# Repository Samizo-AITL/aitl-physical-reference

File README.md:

# 🧩 aitl-physical-reference

This repository provides a **minimal physical reference PCB**  
that anchors abstract control and logic concepts into **real voltage, current, and copper**.

It is intentionally **small, generic, and architecture-agnostic**,  
focusing on **observability, physical constraints, and manufacturability** rather than functionality.

---

## 🔗 Links

| Language | GitHub Pages 🌐 | GitHub 💻 |
|----------|----------------|-----------|
| 🇺🇸 English |  |  |

---

## 🎯 Purpose

The purpose of this board is **not control**, but **grounding**.

- 🔌 Fix abstract logic into **measurable V–I behavior**
- 👁 Provide a **visible and probe-able physical endpoint**
- 🧱 Act as a **lowest-level physical reference**, reusable across systems

This board can be *used by* higher-level architectures  
(control logic, supervisory layers, AI reasoning),  
but it **does not depend on them**.

---

## 🧩 What This Is

This repository contains a **reference PCB**, not a product.

The board includes only elements required to expose  
the relationship between logic and physics:

- 💡 **LED** — observable output state  
- 🧮 **Resistor** — physical constraint (current limitation)  
- 🔘 **Switch** — discrete physical event input  
- 📍 **Test Point** — voltage / current measurement access  
- 📐 **Board outline (Edge.Cuts)** — explicit physical boundary  

Nothing more.

---

## 🖼 Figure Index (Canonical)

All schematics, PCB layouts, and 3D views used in this project are
**normatively indexed and embedded** on the following page:

👉 **Image Index (v0–v3)**  
[https://samizo-aitl.github.io/aitl-physical-reference/docs/img/](https://samizo-aitl.github.io/aitl-physical-reference/docs/img/)

> v3 figures are provided for *derived control reference boards*
> and do not modify the normative v0–v2 physical reference.

---

## 🖼 Physical Reference Overview

### 1️⃣ Schematic (Logical → Physical Mapping)

This schematic defines the **normative logical–physical boundary**:  
a logic-driven output constrained by real voltage and current,  
with explicit measurement access points.

---

### 2️⃣ PCB Layout (Physical Constraints)

The PCB layout exposes the **fixed physical constraints**:

- 🟠 Copper routing and current paths  
- 📦 Component placement tied to observability  
- ⛓ Explicit board boundary (Edge.Cuts)  

This layout is the **authoritative physical truth** for v1.

---

### 3️⃣ 3D View (Embodied Reality)

The 3D view represents the **embodied boundary** between logic and physics:  
real height, real clearances, and real probe access —  
nothing abstracted, nothing implied.

---

## 🚫 What This Is NOT

- ❌ Not a full controller  
- ❌ Not MCU-centric  
- ❌ Not performance-optimized  
- ❌ Not tied to any single architecture or framework  
- ❌ Not a demo board for features  

This repository intentionally avoids *solutions* and focuses on *reference*.

---

## 🧠 Architecture Mapping (Conceptual → Physical)

| Conceptual Role | Physical Element |
|-----------------|------------------|
| Output state    | 💡 LED           |
| Constraint      | 🧮 Resistor      |
| Event input     | 🔘 Switch        |
| Observation     | 📍 Test point    |
| Boundary        | 📐 PCB outline   |

This mapping is the **core value** of the project.

---

## 🗂 Repository Structure

```
aitl-physical-reference/
├─ hardware/
│ └─ kicad/ # KiCad project (schematic / PCB)
├─ bom/
│ └─ bom.csv # Component list (non-CAD)
├─ docs/
│ ├─ Assembly.md # Assembly instructions
│ ├─ TestProcedure.md # Measurement & verification
│ └─ DesignIntent.md # Physical design intent
└─ README.md
```

---

## 📂 Key Artifacts (Reference Entry Points)

### 📄 Documentation
- **Design Intent**  
  [GitHub Page](https://samizo-aitl.github.io/aitl-physical-reference/docs/DesignIntent.html)  
  [Repository](https://github.com/Samizo-AITL/aitl-physical-reference/tree/main/docs/DesignIntent.md)

- **Assembly Instructions**  
  [GitHub Page](https://samizo-aitl.github.io/aitl-physical-reference/docs/Assembly.html)  
  [Repository](https://github.com/Samizo-AITL/aitl-physical-reference/tree/main/docs/Assembly.md)

- **Test & Measurement Procedure**  
  [GitHub Page](https://samizo-aitl.github.io/aitl-physical-reference/docs/TestProcedure.html)  
  [Repository](https://github.com/Samizo-AITL/aitl-physical-reference/tree/main/docs/TestProcedure.md)

### 🧾 Bill of Materials
- **BOM (CSV)**  
  [GitHub Page](https://samizo-aitl.github.io/aitl-physical-reference/bom/bom.csv)  
  [Repository](https://github.com/Samizo-AITL/aitl-physical-reference/blob/main/bom/bom.csv)

### 🧩 Hardware Source (Physical Truth)
- **KiCad Project (Schematic / PCB)**  
  [Repository](https://github.com/Samizo-AITL/aitl-physical-reference/tree/main/hardware/kicad)

---

## 🔧 Build & Assembly Flow

To physically build and use this reference board:

1. 📄 Review **`bom/bom.csv`** and prepare components  
2. 🏭 Manufacture PCB using KiCad data in `hardware/kicad/`  
3. 🛠 Assemble components following **`docs/Assembly.md`**  
4. ⚡ Apply +5V power and observe LED behavior  
5. 📊 Verify voltage/current using **`docs/TestProcedure.md`**

This flow is intentionally simple and repeatable.

---

## 📏 Verification & Measurement

This board is designed to be **measured**, not just powered.

Typical checks:

- 💡 LED ON/OFF state  
- 📍 Forward voltage at test point  
- 🧮 Current limited by resistor  
- 📐 Boundary defined by board outline  

These checks validate the **logic → physics transition**.

---

## 🧰 Toolchain

- 🧩 **CAD**: KiCad  
- 🎨 **Design style**: Minimal, readable, single-layer preferred  
- 📤 **Outputs**: Standard manufacturable Gerber data  

The design favors **clarity over density**.

---

## 🌍 Usage Context

This physical reference can be used in:

- 🎛 Control systems  
- 🧠 Supervisory logic  
- 🎓 Educational hardware  
- 🔁 Logic-to-physical architecture studies  
- 🤖 AITL-based discussions and validation  

It acts as a **ground truth layer**, not a controller.

---

## 📌 Status

- **v0** — Minimal physical reference  
  - 💡 LED  
  - 🧮 Resistor  
  - 🔘 Switch  
  - 📍 Test point  

Future revisions may extend observability,  
but will preserve minimalism.

---

## 🟦 v1 Definition — Physical ↔ Logical Boundary Reference

**v1** extends *aitl-physical-reference* from a passive grounding board  
into a **clearly defined physical–logical boundary reference**.

This version does **not** aim to control, compute, or decide.  
It exists solely to **define where logic ends and physics begins**.

---

### 🎯 Purpose of v1

- 🔗 Define a **clear GPIO ↔ physical boundary**
- 📏 Fix **measurable voltage–current expectations** at that boundary
- 🧭 Provide a **stable reference point** for higher layers (FSM / PID / AI)

v1 answers one question only:

> *“When logic toggles a pin, what does that mean in copper, voltage, and current?”*

---

### 🔌 v1 Scope (Strict)

v1 **adds a boundary**, not intelligence.

**Included**
- 📍 Explicit **logic-level input/output pins**
- 💡 Physical load (LED + R) driven *through* that boundary
- 📊 Documented **expected V–I ranges per node**
- 🧪 Test points tied to logical meaning

**Explicitly excluded**
- ❌ No firmware logic
- ❌ No control algorithm
- ❌ No timing guarantees
- ❌ No optimization

---

### 📐 Boundary Concept

| Layer | Responsibility |
|------|----------------|
| Logical / MCU | State decision, timing, abstraction |
| **v1 Boundary** | **Voltage level, current flow, observability** |
| Physical | Light emission, heat, copper limits |

v1 is the **line**, not the controller.

---

### 📊 Reference Measurement Table (Normative)

| Node | Condition | Expected Voltage | Expected Current | Meaning |
|-----|----------|-----------------|-----------------|--------|
| LOGIC_OUT | High | 3.3–5.0 V | < 1 mA | Logic asserts state |
| LED_NODE | ON | 1.8–2.2 V | 5–10 mA | Physical output active |
| VCC | Nominal | 5.0 V ±5% | — | Power reference |

This table is **normative** in v1.

---

### 🧠 Architectural Role

v1 serves as:

- 🔹 **FSM** — physical state confirmation point  
- 🔹 **PID** — actuator-side reality reference  
- 🔹 **LLM / AI** — grounding layer to prevent abstraction drift  

Higher layers may change.  
**v1 must not.**

---

### 🔒 Stability Rule

Once released:

> **v1 electrical meaning SHALL NOT change.**

Any extension must:
- become **v1.x** (documentation / measurement only), or
- move to **v2** (control-capable reference)

---

### 🏷 Versioning Summary

- 🟢 **v0** — Passive physical reference (LED / R / SW / TP)
- 🔵 **v1** — Logical–physical boundary reference
- 🟣 **v2** — Control-capable execution reference (FSM / PID)

---

## 🔖 GPIO Naming Rule (v1)

GPIO names in **v1** are **semantic and directional**.  
They describe **what crosses the boundary**, not how it is implemented.

### 📛 Naming Format

```
<ROLE>_<DIRECTION>
```

- **ROLE**: logical meaning at the boundary  
- **DIRECTION**: signal direction *from logic perspective*

### 📌 Standard Roles

| Name | Meaning |
|-----|--------|
| `LOGIC_OUT` | Logic asserts a physical state |
| `LOGIC_IN` | Logic observes a physical condition |
| `PWR_IN` | External power reference |
| `GND` | Electrical ground |

### 🔄 Direction Definition

- `_OUT` : logic → physical  
- `_IN`  : physical → logic  

> Example: `LOGIC_OUT` means  
> “Logic drives voltage/current into the physical layer.”

### 🚫 Prohibited in v1

- ❌ MCU-specific names (`PA0`, `GPIO23`)
- ❌ Functional assumptions (`LED_CTRL`, `PWM_OUT`)
- ❌ Timing semantics (`CLK`, `SYNC`)

v1 names must remain **architecture-agnostic and timeless**.

---

## 🟣 v2 Definition — Executable Physical Loop Reference

**v2** realizes the v1 physical–logical boundary  
as a **manufacturable, observable, and DRC-clean physical loop**.

While v1 defines *what the boundary means*,  
v2 defines *how that meaning exists in copper*.

---

### 🎯 Purpose of v2

- 🧱 Fix the **entire V–I loop** as a physical fact
- 👁 Preserve **observability at every critical node**
- 🏭 Ensure **manufacturability (DRC clean, Edge.Cuts defined)**
- 🚫 Still **no control logic, no firmware, no optimization**

v2 answers one question only:

> *“If we freeze the physical loop itself, what remains controllable?”*

---

### 🔌 v2 Scope (Strict)

**Included**
- 📐 Explicit **board outline (Edge.Cuts)**
- 🔁 Single, closed **physical current loop**
- 📍 Test points that do **not disturb** the loop
- 🧮 Current-limiting elements as physical constraints

**Explicitly excluded**
- ❌ No MCU
- ❌ No GPIO semantics
- ❌ No feedback or timing logic
- ❌ No intelligence

---

### 🧠 Architectural Role of v2

| Layer | Role |
|------|------|
| v1 | Normative boundary definition |
| **v2** | **Executable physical ground truth** |
| v3+ | Control, supervision, adaptation |

v2 is the **last layer before control begins**.

---

### 🔒 Stability Rule (v2)

Once released:

> **The physical loop topology and V–I meaning SHALL NOT change.**

Any change must advance to **v3**.

---

### 🏷 Versioning Summary (Updated)

- 🟢 **v0** — Passive physical reference
- 🔵 **v1** — Physical ↔ Logical boundary definition
- 🟣 **v2** — Executable physical loop reference (DRC clean)
- 🔴 **v3** — Control insertion reference (FSM / PID)

---

## 🔴 v3 — Derived Control Reference (External)

**v3 is NOT part of the aitl-physical-reference core.**

It is a *derived hardware reference* that **inserts minimal control**
into the **frozen physical loop defined by v2**.

- v0–v2: normative physical reference (this repository)
- v3: downstream control experiment (separate hardware directory)

The authoritative source for v3 is:

👉 hardware/kicad/aitl-physical-control  
👉 See **Fig.10–Fig.12** in the Image Index

v0–v2 remain **unchanged and normative** regardless of v3 evolution.

---

## 👤 Author

| 📌 Item | Details |
|--------|---------|
| **Name** | Shinichi Samizo |
| **Expertise** | Semiconductor devices (logic, memory, high-voltage mixed-signal)<br>Thin-film piezo actuators for inkjet systems<br>Printhead productization, BOM management, ISO training |
| **GitHub** |  |

---

## 📄 License

| 📌 Item | License | Description |
|--------|---------|-------------|
| **Source Code** | [**MIT License**](https://opensource.org/licenses/MIT) | Free to use, modify, and redistribute |
| **Text Materials** | [**CC BY 4.0**](https://creativecommons.org/licenses/by/4.0/) or [**CC BY-SA 4.0**](https://creativecommons.org/licenses/by-sa/4.0/) | Attribution required; share-alike applies for BY-SA |
| **Figures & Diagrams** | [**CC BY-NC 4.0**](https://creativecommons.org/licenses/by-nc/4.0/) | Non-commercial use only |
| **External References** | Follow the original license | Cite the original source properly |

---

## 💬 Feedback

> Suggestions, improvements, and discussions are welcome via GitHub Discussions.

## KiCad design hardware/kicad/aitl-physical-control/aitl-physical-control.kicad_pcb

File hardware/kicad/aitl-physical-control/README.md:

# aitl-physical-control

Minimal **physical control reference board (v3)** for AITL.  
This project adds **one controllable element** to the frozen physical loop defined in
`aitl-physical-reference`, without changing the loop topology.

---

## Purpose

- Provide a **minimal control insertion** into a fixed V–I loop
- Observe how **continuous control** affects current and voltage
- Keep the physical loop **non-branching and observable**

This board is **not** a controller, MCU platform, or application PCB.

---

## What This Board Is

- Single closed loop: `+5V → RV → R → LED → GND`
- One control element: **potentiometer (RV1)**
- Explicit observation points:
  - **TP1**: +5V
  - **TP2**: GND
- DRC clean, manufacturable

---

## What This Board Is Not

- No MCU
- No GPIO semantics
- No feedback control logic
- No timing or intelligence

Those belong to higher layers.

---

## Schematic Overview

- **RV1**: Trimmer potentiometer (used as 2-terminal variable resistor)
- **R1**: Current limiting resistor
- **D1**: LED (visual current indicator)
- **TP1**: +5V test point
- **TP2**: GND test point

---

## PCB Notes

- RV1 wiper is **physically shorted** to one terminal (intentional)
- Single-layer routing (F.Cu)
- No ground plane required
- Loop integrity preserved from v2

---

## Files

```
hardware/kicad/aitl-physical-control/
├─ aitl-physical-control.kicad_pro
├─ aitl-physical-control.kicad_sch
├─ aitl-physical-control.kicad_pcb
└─ fp-info-cache
```

---

## Usage

1. Supply +5V at TP1
2. Observe LED brightness
3. Rotate RV1 to vary current
4. Measure voltage/current at TP1 / TP2

---

## Position in AITL Hardware Stack

- `aitl-physical-reference` : frozen physical loop (v2)
- **`aitl-physical-control` : minimal control insertion (v3)**
- Higher layers (FSM / PID / MCU) build on top of this

---

## Status

- v3 complete
- No further revisions planned
- Changes should be introduced as **experiments**, not new versions

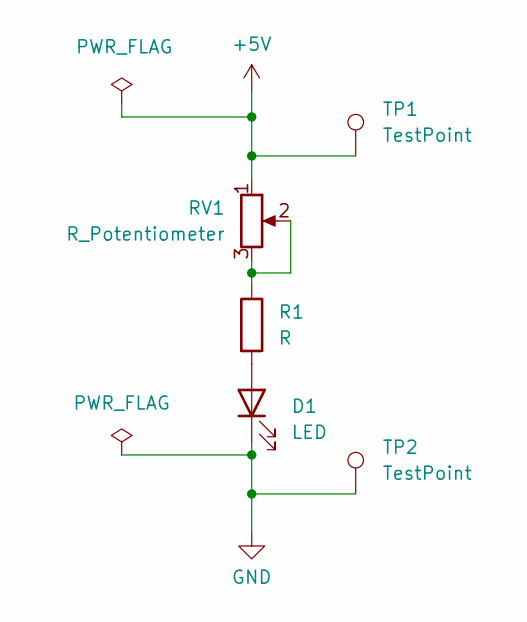
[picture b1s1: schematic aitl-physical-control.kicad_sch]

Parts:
D1: LED; LED_0603_1608Metric
R1: R; R_0603_1608Metric
RV1: R_Potentiometer; Potentiometer_Bourns_3296W_Vertical
TP1, TP2: TestPoint; TestPoint_Pad_D1.0mm

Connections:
+5V: RV1.1, TP1.1
GND: D1.1 (K), TP2.1
unnamed: D1.2 (A), R1.2
unnamed: R1.1, RV1.2, RV1.3

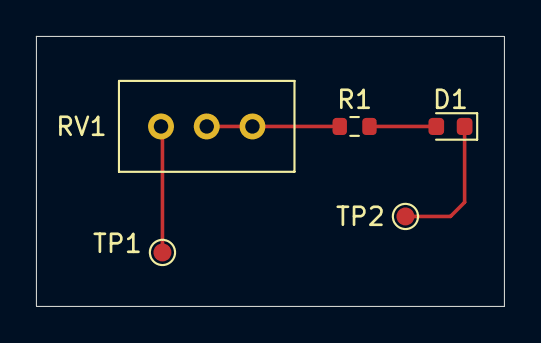
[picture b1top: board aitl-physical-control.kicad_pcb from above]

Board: 2 copper layers, 26.0 x 15.0 mm, 5 parts (0 on the bottom side), 4 nets.

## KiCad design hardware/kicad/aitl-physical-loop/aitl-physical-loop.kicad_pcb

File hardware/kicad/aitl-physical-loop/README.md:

---
title: "aitl-physical-loop (KiCad Source)"
description: "KiCad source files for the executable physical loop reference (v2) in the AITL physical reference project."
---

# 🧩 aitl-physical-loop — KiCad Source

This directory contains the **authoritative KiCad source files**
for the **v2 executable physical loop reference** of the
*aitl-physical-reference* project.

This design represents a **closed, manufacturable V–I loop**
that is **DRC-clean, observable, and topology-stable**.

It is **not** a controller, and it contains **no logic or firmware**.

---

## 🎯 Role in the Architecture

| Layer | Meaning |
|------|--------|
| v1 | Logical ↔ physical boundary definition |
| **v2 (this board)** | **Executable physical ground truth** |
| v3+ | Control / supervision / adaptation |

This board answers one question only:

> **“What does a frozen physical current loop look like in real copper?”**

---

## 📂 Contents

| File | Description |
|-----|------------|
| `aitl-physical-loop.kicad_pro` | KiCad project file |
| `aitl-physical-loop.kicad_sch` | Schematic (logical definition of the loop) |
| `aitl-physical-loop.kicad_pcb` | PCB layout (physical realization, Edge.Cuts defined) |
| `aitl-physical-loop.kicad_prl` | KiCad project local settings |
| `fp-info-cache` | KiCad footprint cache |

These files together define the **single source of physical truth** for v2.

---

## 🖼 Reference Figures

All figures derived from this KiCad project
(schematic, PCB layout, 3D view) are **canonically indexed and embedded**
on the following page:

👉 **Figure Index (v0–v2)**  
https://samizo-aitl.github.io/aitl-physical-reference/docs/img/

Referenced figures include:

- **Fig.07** — v2 Schematic  
- **Fig.08** — v2 PCB Layout  
- **Fig.09** — v2 3D View  

Do **not** duplicate images here.  
The figure index is the **single normative reference**.

---

## 🔒 Stability Rule (v2)

Once released:

> **The physical loop topology and its V–I meaning SHALL NOT change.**

Any modification that alters:
- current path,
- constraint elements,
- observability points, or
- board outline

**must advance the version to v3**.

---

## 🚫 What This Is NOT

- ❌ Not a microcontroller board
- ❌ Not GPIO-defined logic
- ❌ Not feedback or control capable
- ❌ Not optimized for size or cost

This directory exists to preserve **physical meaning**, not behavior.

---

## 🔧 Toolchain

- **CAD**: KiCad 9.x
- **Design goal**: Clarity, observability, manufacturability
- **Status**: DRC clean, Edge.Cuts defined

---

## 🔗 Top-Level Context

For project intent, documentation, and measurement procedures, see:

- Project root (README):  
  https://samizo-aitl.github.io/aitl-physical-reference/

- Design intent:  
  https://samizo-aitl.github.io/aitl-physical-reference/docs/DesignIntent.html

---

## 👤 Author

**Shinichi Samizo**  
Semiconductor devices, mixed-signal systems, physical–logical architecture

GitHub: https://github.com/Samizo-AITL

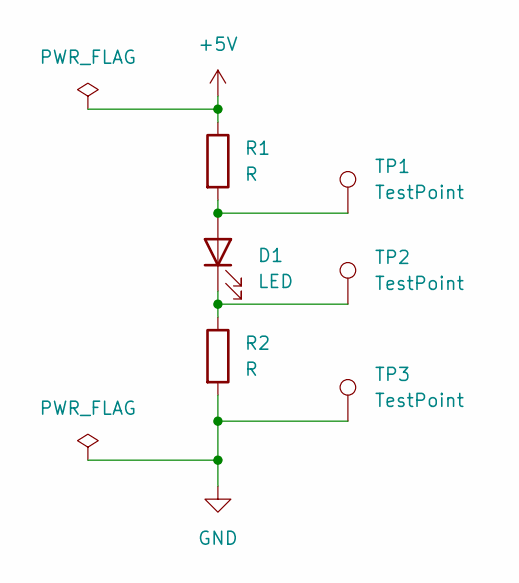
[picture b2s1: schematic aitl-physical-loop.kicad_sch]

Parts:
D1: LED; LED_0603_1608Metric
R1, R2: R; R_0603_1608Metric
TP1, TP2, TP3: TestPoint; TestPoint_Pad_D1.0mm

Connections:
+5V: R1.1
GND: R2.2, TP3.1
unnamed: D1.2 (A), R1.2, TP1.1
unnamed: D1.1 (K), R2.1, TP2.1

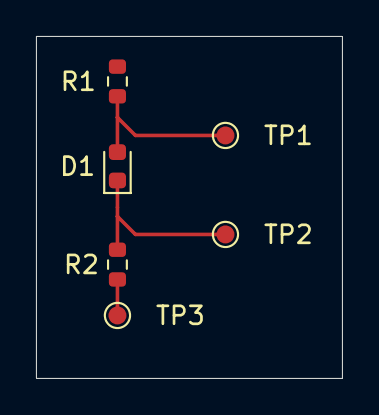
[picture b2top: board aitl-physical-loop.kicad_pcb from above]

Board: 2 copper layers, 17.0 x 19.0 mm, 6 parts (0 on the bottom side), 3 nets.

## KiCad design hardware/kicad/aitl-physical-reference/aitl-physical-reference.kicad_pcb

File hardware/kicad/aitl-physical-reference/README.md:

---
title: "aitl-control-reference"
description: "A control architecture reference that defines FSM and PID roles grounded to physical truth."
---

# 🎛 aitl-control-reference

This repository provides a **control architecture reference**  
within the **AITL (Architecture for Integrated Technology Logic)** framework.

It defines **what control means**,  
not how optimized, fast, or intelligent it is.

This project exists to **fix responsibility, structure, and observability**  
of control systems before implementation details are considered.

---

## 🎯 Purpose

The purpose of this repository is **not implementation**, but **definition**.

- 🧭 Define **control roles** (FSM vs PID)
- 🔗 Bind control outputs to **physical truth**
- 📏 Ensure control behavior is **observable and explainable**
- 🧱 Provide a **stable reference** reusable across systems

This repository depends on physical grounding provided by:

- 👉 **`aitl-physical-reference`**

---

## 🧠 Relation to AITL

Within AITL, this repository represents the **Control Reference Layer**.

| AITL Layer | Responsibility |
|-----------|----------------|
| Reasoning | Strategy, redesign, adaptation |
| **Control Reference (this repo)** | **FSM / PID structure and responsibility** |
| Physical Reference | Voltage, current, copper, measurement |

This layer does **not** reason  
and does **not** implement hardware truth.

---

## 📌 Status

### 🟢 v0 — Experimental Control Reference

**v0** represents the **exploratory phase**.

Characteristics:
- FSM and PID may coexist without strict separation
- Control logic may be mixed or simplified
- Structure may change freely
- Intended for **experimentation and understanding**

v0 answers:
> *“What kind of control structure might work?”*

v0 is **allowed to be messy**.

---

## 🟦 v1 Definition — Control Architecture Reference

**v1** formalizes this repository as a  
**control architecture reference**, not an implementation showcase.

This version fixes **what control means**,  
not how fast, smart, or optimal it is.

---

### 🎯 Purpose of v1

- 🎛 Define **clear responsibility separation** between FSM and PID
- 🔗 Bind control outputs to **physical reality via physical-reference**
- 📏 Make control behavior **observable, explainable, and reproducible**

v1 answers one question only:

> *“What is control, and where does each role end?”*

---

### 🧠 Control Architecture Scope (v1)

v1 is strictly architectural.

**Included**
- 🧭 **FSM (Finite State Machine)**  
  - Mode selection  
  - State transitions  
  - Supervisory decisions
- 📐 **PID (or equivalent continuous controller)**  
  - Continuous variable control  
  - Stability and response shaping
- 🔌 Explicit dependency on **`aitl-physical-reference`** for I/O grounding

**Explicitly excluded**
- ❌ Hardware optimization
- ❌ Performance tuning
- ❌ Application-specific logic
- ❌ AI / LLM-based redesign

---

### 🧩 Responsibility Separation

| Layer | Responsibility |
|------|----------------|
| FSM | Discrete mode and state decisions |
| PID | Continuous control within a mode |
| Physical Reference | Voltage, current, and physical truth |

No layer overlaps responsibility.

---

### 🔗 Relation to Physical Reference

All control outputs and observations in v1:

- MUST terminate at **`aitl-physical-reference`**
- MUST be explainable in **voltage, current, and measurement**
- MUST avoid abstract-only signals

If it cannot be measured physically,  
it is **out of scope** for v1.

---

### 📊 Observability Rule

In v1:

- FSM state must be **externally identifiable**
- PID output must be **physically observable**
- Control intent must be visible **without firmware inspection**

Control exists **only when it is observable**.

---

### 🔒 Stability Rule

Once released as v1:

- Architectural roles **shall not change**
- FSM / PID separation **shall not blur**
- Physical dependency **shall remain explicit**

Extensions must become **v1.x** (documentation only)  
or move to **v2**.

---

## 🏷 Versioning Summary

- 🟢 **v0** — Experimental / exploratory control reference
- 🔵 **v1** — Control architecture reference (this definition)
- 🟣 **v2** — Adaptive or AI-assisted control (future)

---

## 🌍 Usage Context

This control reference may be used for:

- 🎛 Control system design studies
- 🧠 FSM / PID role education
- 🔁 Architecture validation with physical reference
- 🤖 AITL-based control discussions

It is **not** a controller, firmware, or product.

---

## 👤 Author

| Item | Details |
|-----|--------|
| **Name** | Shinichi Samizo |
| **GitHub** | https://github.com/Samizo-AITL |

---

## 📄 License

This repository follows the same **hybrid license policy**  
as other AITL reference projects.

Refer to the root license declaration for details.

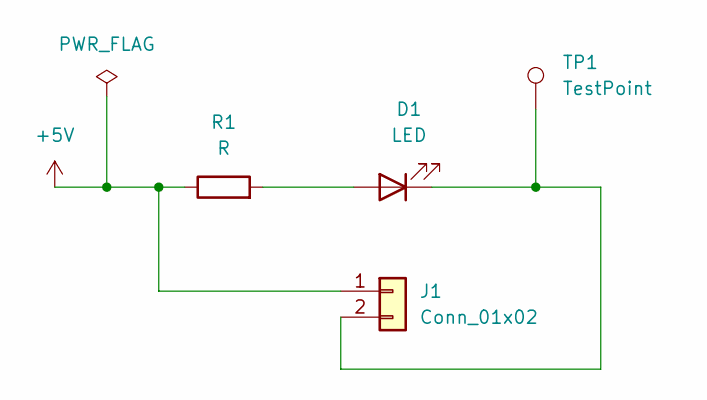
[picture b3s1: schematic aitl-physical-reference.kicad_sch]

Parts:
D1: LED; LED_0603_1608Metric
J1: Conn_01x02; PinHeader_1x02_P2.54mm_Vertical
R1: R; R_0603_1608Metric
TP1: TestPoint; TestPoint_Pad_1.0x1.0mm

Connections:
+5V: J1.1, R1.1
unnamed: D1.2 (A), R1.2
unnamed: D1.1 (K), J1.2, TP1.1

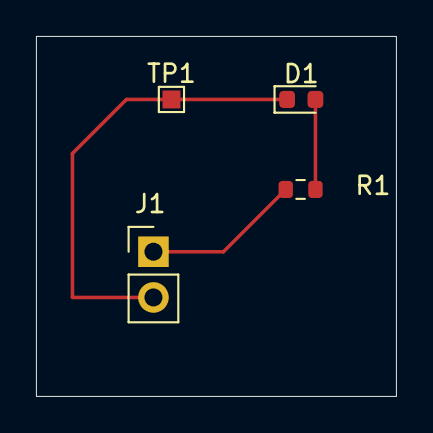
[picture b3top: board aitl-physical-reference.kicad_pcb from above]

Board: 2 copper layers, 20.0 x 20.0 mm, 4 parts (0 on the bottom side), 3 nets.
